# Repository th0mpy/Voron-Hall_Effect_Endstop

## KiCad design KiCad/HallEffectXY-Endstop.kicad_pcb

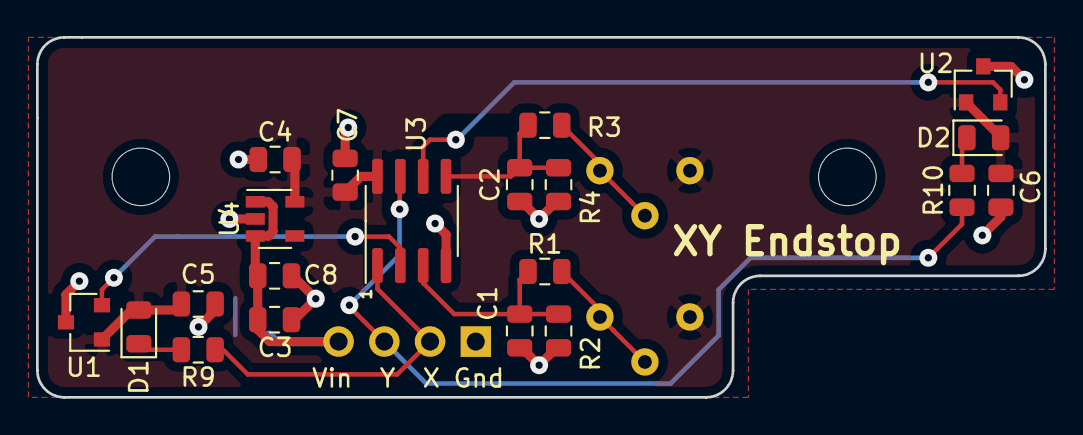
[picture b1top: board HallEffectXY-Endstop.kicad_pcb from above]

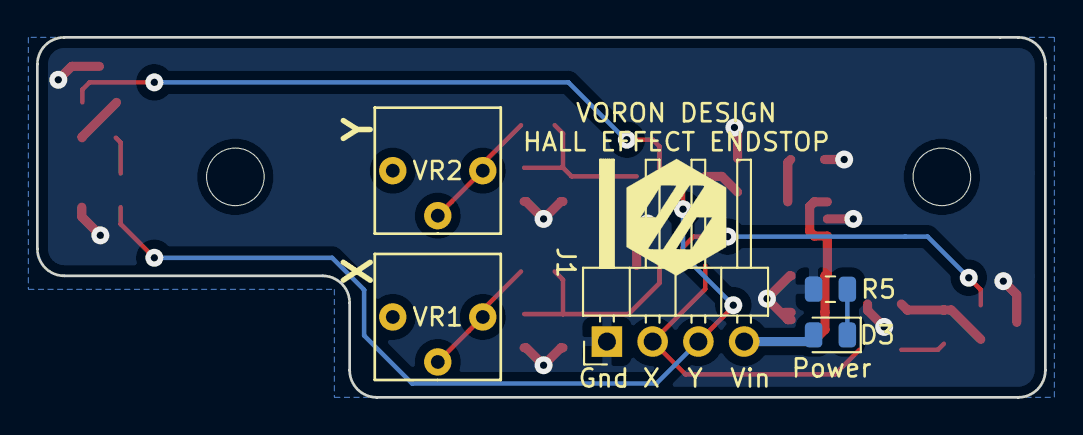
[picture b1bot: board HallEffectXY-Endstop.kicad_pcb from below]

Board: 2 copper layers, 56.0 x 20.0 mm, 25 parts (5 on the bottom side), 14 nets.

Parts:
C1, C2: 0.1uF; C_0805_2012Metric
C3, C4, C5, C6, C7: 1uF; C_0805_2012Metric
C8: 10uF; C_0805_2012Metric
D1, D2, D3: LED_0805; LED_0805_2012Metric
J1: CONN_01X04; PinHeader_1x04_P2.54mm_Horizontal
R1, R3, R5, R9, R10: 1.00K; R_0805_2012Metric
R2, R4: 10.0k; R_0805_2012Metric
U1, U2: SS39ET; SOT-23
U3: LM393; SOIC-8_3.9x4.9mm_P1.27mm
U4: AP2127K-3.3; SOT-23-5
VR1, VR2: 10.0K; CT6EP103

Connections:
+3V3: C4.1, C5.1, C6.1, C7.2, D1.2, D2.2, U1.1, U2.1, U3.8, U4.5, VR1.3, VR2.3
+5V: C3.1, C8.1, D3.2, J1.4, U4.1, U4.3
GND: C1.2, C2.2, C3.2, C4.2, C5.2, C6.2, C7.1, C8.2, J1.1, R2.2, R4.2, R5.1, U1.3, U2.3, U3.4, U4.2
unnamed: C1.1, R1.1, R2.1, U3.3
unnamed: C2.1, R3.1, R4.1, U3.5
unnamed: D1.1, R9.1
unnamed: D2.1, R10.1
unnamed: D3.1, R5.2
unnamed: R1.2, VR1.1, VR1.2
unnamed: R3.2, VR2.1, VR2.2
unnamed: U1.2, U3.2
unnamed: U2.2, U3.6
X_SIG: J1.2, R9.2, U3.1
Y_SIG: J1.3, R10.2, U3.7

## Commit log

2023-01-02 Initial upload
